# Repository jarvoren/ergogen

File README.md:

Monster keybord.
Pcb mounted switches and overall very basic version of the keyboard.
Ergogen used in the build in repo. Actually had a lot of problems with this one.

Will improve when i regain the will to live after this one.

Zmk firmware : 
https://github.com/jarvoren/zmk-config-monster

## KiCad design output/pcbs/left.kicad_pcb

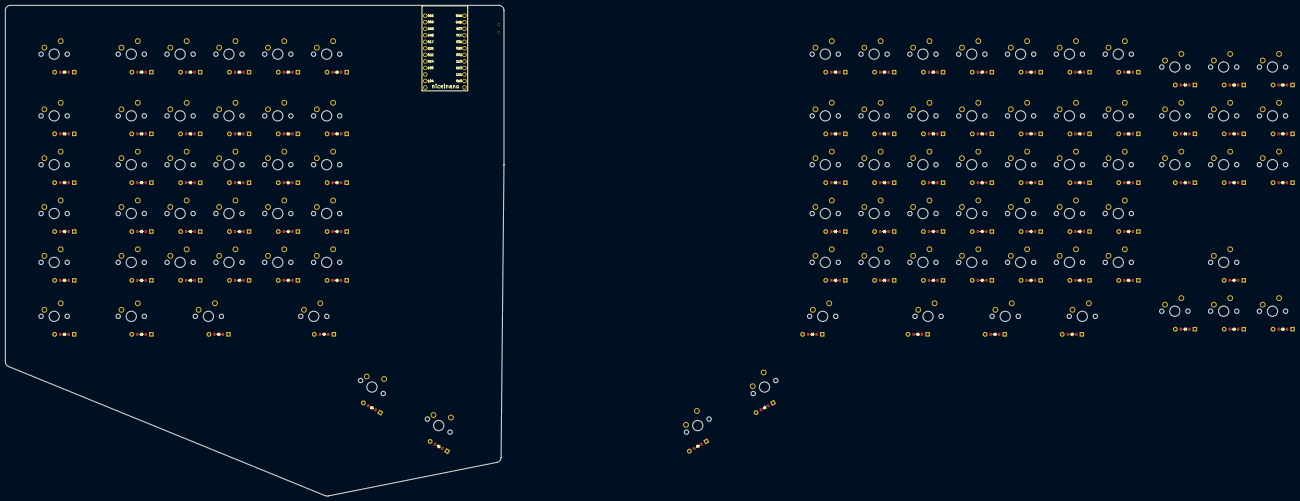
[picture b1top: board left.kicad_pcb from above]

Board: 2 copper layers, 194.0 x 190.9 mm, 183 parts (0 on the bottom side), 109 nets, no tracks yet.

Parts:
B1: SW_TACT_ALPS_SKQGABE010
D1, D2, D3, D4, D5, D6, D7, D8, D9, D10, D11, D12, D13, D14, D15, D16, D17, D18, D19, D20, D21, D22, D23, D24, D25, D26, D27, D28, D29, D30, D31, D32, D33, D34, D35, D36, D37, D38, D39, D40, D41, D42, D43, D44, D45, D46, D47, D48, D49, D50, D51, D52, D53, D54, D55, D56, D57, D58, D59, D60, D61, D62, D63, D64, D65, D66, D67, D68, D69, D70, D71, D72, D73, D74, D75, D76, D77, D78, D79, D80, D81, D82, D83, D84, D85, D86, D87, D88, D89, D90: ComboDiode
MCU1: nice_nano
S1, S2, S3, S4, S5, S6, S7, S8, S9, S10, S11, S12, S13, S14, S15, S16, S17, S18, S19, S20, S21, S22, S23, S24, S25, S26, S27, S28, S29, S30, S31, S32, S33, S34, S35, S36, S37, S38, S39, S40, S41, S42, S43, S44, S45, S46, S47, S48, S49, S50, S51, S52, S53, S54, S55, S56, S57, S58, S59, S60, S61, S62, S63, S64, S65, S66, S67, S68, S69, S70, S71, S72, S73, S74, S75, S76, S77, S78, S79, S80, S81, S82, S83, S84, S85, S86, S87, S88, S89, S90: MX
T1: SPDT_C128955

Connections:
1qazcol_asdrow: D2.2, S2.2
1qazcol_numberrow: D4.2, S4.2
1qazcol_qwerow: D3.2, S3.2
1qazcol_zxcrow: D1.2, S1.2
2wsxcol_asdrow: D6.2, S6.2
2wsxcol_numberrow: D8.2, S8.2
2wsxcol_qwerow: D7.2, S7.2
2wsxcol_zxcrow: D5.2, S5.2
3edccol_asdrow: D10.2, S10.2
3edccol_numberrow: D12.2, S12.2
3edccol_qwerow: D11.2, S11.2
3edccol_zxcrow: D9.2, S9.2
4rfvcol_asdrow: D14.2, S14.2
4rfvcol_numberrow: D16.2, S16.2
4rfvcol_qwerow: D15.2, S15.2
4rfvcol_zxcrow: D13.2, S13.2
5tgbcol_asdrow: D18.2, S18.2
5tgbcol_numberrow: D20.2, S20.2
5tgbcol_qwerow: D19.2, S19.2
5tgbcol_zxcrow: D17.2, S17.2
GND: B1.1, MCU1.3, MCU1.4, MCU1.23
P002: D27.1, D31.1, D35.1, D39.1, D43.1, D47.1, D51.1, D73.1, D78.1, D82.1, MCU1.18, S5.1, S6.1, S7.1, S8.1, S55.1
P006: D53.1, D54.1, D55.1, D56.1, D57.1, D58.1, MCU1.1, S25.1, S26.1, S27.1, S28.1, S65.1
P008: D4.1, D8.1, D12.1, D16.1, D20.1, D24.1, MCU1.2, S29.1, S30.1, S31.1, S32.1, S66.1
P011: MCU1.10, S72.1, S73.1, S74.1, S75.1
P017: D3.1, D7.1, D11.1, D15.1, D19.1, D23.1, MCU1.5, S33.1, S34.1, S35.1, S36.1, S67.1
P020: D2.1, D6.1, D10.1, D14.1, D18.1, D22.1, MCU1.6, S37.1, S38.1, S39.1, S40.1, S68.1
P022: D1.1, D5.1, D9.1, D13.1, D17.1, D21.1, MCU1.7, S41.1, S42.1, S43.1, S44.1, S69.1
P024: D59.1, D60.1, D61.1, D62.1, D63.1, D64.1, MCU1.8, S45.1, S46.1, S47.1, S48.1, S70.1
P029: D28.1, D32.1, D36.1, D40.1, D44.1, D48.1, D52.1, D74.1, D79.1, D83.1, MCU1.19, S1.1, S2.1, S3.1, S4.1, S54.1
P031: D65.1, D66.1, D67.1, D68.1, D69.1, D70.1, D71.1, D75.1, D80.1, D84.1, MCU1.20, S21.1, S22.1, S23.1, S24.1, S53.1, S59.1
P100: MCU1.9, S49.1, S50.1, S51.1, S52.1, S71.1, S85.1
P104: MCU1.11, S76.1, S77.1, S78.1, S79.1, S80.1
P106: MCU1.12, S81.1, S82.1, S83.1, S84.1
P111: D72.1, D76.1, D81.1, D85.1, D86.1, D87.1, D88.1, D89.1, D90.1, MCU1.15, S17.1, S18.1, S19.1, S20.1, S58.1
P113: D25.1, D29.1, D33.1, D37.1, D41.1, D45.1, D49.1, D77.1, MCU1.16, S13.1, S14.1, S15.1, S16.1, S57.1
P115: D26.1, D30.1, D34.1, D38.1, D42.1, D46.1, D50.1, MCU1.17, S9.1, S10.1, S11.1, S12.1, S56.1
RAW: MCU1.24, T1.2
RST: B1.2, MCU1.22
alt_thumbrow: D61.2, S61.2
ctrl2_thumbrow: D63.2, S63.2
ctrl_thumbrow: D59.2, S59.2
esc_escaperow: D53.2, S53.2
f1_escaperow: D54.2, S54.2
f2_escaperow: D55.2, S55.2
f3_escaperow: D56.2, S56.2
f4_escaperow: D57.2, S57.2
f5_escaperow: D58.2, S58.2
f6_one: D65.2, S65.2
f7_one: D66.2, S66.2
f8_one: D67.2, S67.2
f9_one: D68.2, S68.2
f10_one: D69.2, S69.2
f11_one: D70.2, S70.2
f12_one: D71.2, S71.2
ikcol_hjkrow: D34.2, S34.2
ikcol_nmrow: D33.2, S33.2
ikcol_numberrow: D36.2, S36.2
ikcol_yuirow: D35.2, S35.2
left_del: D73.2, S73.2
left_down: D72.2, S72.2
left_ins: D74.2, S74.2
left_macro: D75.2, S75.2
minuscol_hjkrow: D46.2, S46.2
minuscol_nmrow: D45.2, S45.2
minuscol_numberrow: D48.2, S48.2
minuscol_yuirow: D47.2, S47.2
mirror_alt_thumbrow: D87.2, S87.2
mirror_ctrl2_thumbrow: D89.2, S89.2
mirror_ctrl_thumbrow: D85.2, S85.2
mirror_space_thumbrow: D88.2, S88.2
mirror_thumbkey_thumbrow: D90.2, S90.2
mirror_winkey_thumbrow: D86.2, S86.2
olcol_hjkrow: D38.2, S38.2
olcol_nmrow: D37.2, S37.2
olcol_numberrow: D40.2, S40.2
olcol_yuirow: D39.2, S39.2
pcol_hjkrow: D42.2, S42.2
pcol_nmrow: D41.2, S41.2
pcol_numberrow: D44.2, S44.2
pcol_yuirow: D43.2, S43.2
pluscol_hjkrow: D50.2, S50.2
pluscol_nmrow: D49.2, S49.2
pluscol_numberrow: D52.2, S52.2
pluscol_yuirow: D51.2, S51.2
right_del: D82.2, S82.2
right_down: D81.2, S81.2
right_ins: D83.2, S83.2
right_macro: D84.2, S84.2
space_thumbrow: D62.2, S62.2
tabcapsshift_caps: D23.2, S23.2
tabcapsshift_shift: D24.2, S24.2
tabcapsshift_tab: D22.2, S22.2
tabcapsshift_tylda: D21.2, S21.2
thumbkey_thumbrow: D64.2, S64.2
ujmcol_hjkrow: D30.2, S30.2
ujmcol_nmrow: D29.2, S29.2
ujmcol_numberrow: D32.2, S32.2
ujmcol_yuirow: D31.2, S31.2
updown_del: D78.2, S78.2
updown_down: D76.2, S76.2
updown_ins: D79.2, S79.2
updown_macro: D80.2, S80.2
updown_up: D77.2, S77.2
winkey_thumbrow: D60.2, S60.2
yhncol_hjkrow: D26.2, S26.2
yhncol_nmrow: D25.2, S25.2
yhncol_numberrow: D28.2, S28.2
yhncol_yuirow: D27.2, S27.2

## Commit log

2024-10-05 move folders around and initial keyboard plan
    Move folders and create initial keyboard plan
2024-10-06 pcb: include nano micro comunity file and fix generation
2024-10-10 wip: add pcbs and wireing scheme
2024-10-11 leftpcb: finished wireing left pcb
    Moving on from ergogen to kicad. Add wireing for pcb and moving pcb to
    finished folder.
2024-10-14 folder cleanup and wired pcbs upload
2024-10-25 finalize v1
    Final version of monster keyboard pcb. Ergogen generated files needed
    touchups. Stl files need work - currently dropped from v1.
2024-11-05 fix drawings for connectors
2024-11-05 foto: add foto of finished version
